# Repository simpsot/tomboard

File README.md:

# tomboard
My 34 split keyboard design. This is a learning project, so don't judge :-).

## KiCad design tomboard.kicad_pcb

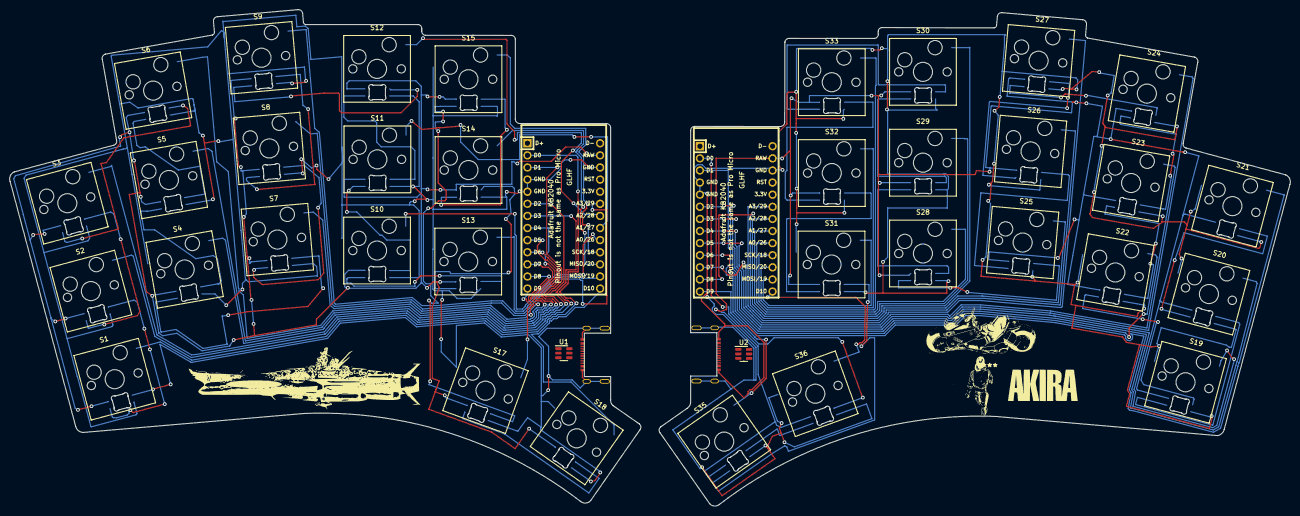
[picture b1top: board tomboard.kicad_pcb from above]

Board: 2 copper layers, 268.6 x 104.1 mm, 40 parts (0 on the bottom side), 75 nets.

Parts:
J0, J1: USB_C_Receptacle_USB2.0; USB-C_C168688
MCU1, MCU2: KB2040; kb2040
S1, S2, S3, S4, S5, S6, S7, S8, S9, S10, S11, S12, S13, S14, S15, S17, S18, S19, S20, S21, S22, S23, S24, S25, S26, S27, S28, S29, S30, S31, S32, S33, S35, S36: MX_SK6182; MX_1.00u_PCB_KailhSocket_mini-led
U1, U2: USBLC6-2SC6; SOT-23-6

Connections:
/+5v: MCU1.15 (RAW), S1.6 (VDD), S2.6 (VDD), S3.6 (VDD), S4.6 (VDD), S5.6 (VDD), S6.6 (VDD), S7.6 (VDD), S8.6 (VDD), S9.6 (VDD), S10.6 (VDD), S11.6 (VDD), S12.6 (VDD), S13.6 (VDD), S14.6 (VDD), S15.6 (VDD), S17.6 (VDD), S18.6 (VDD)
/GND: J0.A1 (GND), J0.S1 (SHIELD), MCU1.4 (GND), MCU1.5 (GND), MCU1.16 (GND), S1.1, S1.3 (VSS), S2.1, S2.3 (VSS), S3.1, S3.3 (VSS), S4.1, S4.3 (VSS), S5.1, S5.3 (VSS), S6.1, S6.3 (VSS), S7.1, S7.3 (VSS), S8.1, S8.3 (VSS), S9.1, S9.3 (VSS), S10.1, S10.3 (VSS), S11.1, S11.3 (VSS), S12.1, S12.3 (VSS), S13.1, S13.3 (VSS), S14.1, S14.3 (VSS), S15.1, S15.3 (VSS), S17.1, S17.3 (VSS), S18.1, S18.3 (VSS)
/led: MCU1.2 (D0), S1.4 (DIN)
/matrix_index_bottom: MCU1.22 (A0/26), S10.2
/matrix_index_home: MCU1.21 (A1/27), S11.2
/matrix_index_top: MCU1.20 (A2/28), S12.2
/matrix_inner_bottom: MCU1.25 (MOSI/19), S13.2
/matrix_inner_home: MCU1.24 (MISO/20), S14.2
/matrix_inner_top: MCU1.23 (SCK/18), S15.2
/matrix_middle_bottom: MCU1.12 (D8), S7.2
/matrix_middle_home: MCU1.11 (D7), S8.2
/matrix_middle_top: MCU1.19 (A3/29), S9.2
/matrix_pinky_bottom: MCU1.7 (D3), S1.2
/matrix_pinky_home: MCU1.6 (D2), S2.2
/matrix_pinky_top: MCU1.3 (D1), S3.2
/matrix_ring_bottom: MCU1.10 (D6), S4.2
/matrix_ring_home: MCU1.9 (D5), S5.2
/matrix_ring_top: MCU1.8 (D4), S6.2
/r_+5v: MCU2.15 (RAW), S19.6 (VDD), S20.6 (VDD), S21.6 (VDD), S22.6 (VDD), S23.6 (VDD), S24.6 (VDD), S25.6 (VDD), S26.6 (VDD), S27.6 (VDD), S28.6 (VDD), S29.6 (VDD), S30.6 (VDD), S31.6 (VDD), S32.6 (VDD), S33.6 (VDD), S35.6 (VDD), S36.6 (VDD)
/r_GND: J1.A1 (GND), J1.S1 (SHIELD), MCU2.4 (GND), MCU2.5 (GND), MCU2.16 (GND), S19.1, S19.3 (VSS), S20.1, S20.3 (VSS), S21.1, S21.3 (VSS), S22.1, S22.3 (VSS), S23.1, S23.3 (VSS), S24.1, S24.3 (VSS), S25.1, S25.3 (VSS), S26.1, S26.3 (VSS), S27.1, S27.3 (VSS), S28.1, S28.3 (VSS), S29.1, S29.3 (VSS), S30.1, S30.3 (VSS), S31.1, S31.3 (VSS), S32.1, S32.3 (VSS), S33.1, S33.3 (VSS), S35.1, S35.3 (VSS), S36.1, S36.3 (VSS), U2.2 (GND)
/r_VCC: J1.A4 (VBUS), MCU2.18 (3.3v), U2.5 (VBUS)
/r_led: MCU2.2 (D0), S36.4 (DIN)
/r_matrix_index_bottom: MCU2.22 (A0/26), S28.2
/r_matrix_index_home: MCU2.21 (A1/27), S29.2
/r_matrix_index_top: MCU2.20 (A2/28), S30.2
/r_matrix_inner_bottom: MCU2.25 (MOSI/19), S31.2
/r_matrix_inner_home: MCU2.24 (MISO/20), S32.2
/r_matrix_inner_top: MCU2.23 (SCK/18), S33.2
/r_matrix_middle_bottom: MCU2.12 (D8), S25.2
/r_matrix_middle_home: MCU2.19 (A3/29), S26.2
/r_matrix_middle_top: MCU2.11 (D7), S27.2
/r_matrix_pinky_bottom: MCU2.7 (D3), S19.2
/r_matrix_pinky_home: MCU2.6 (D2), S20.2
/r_matrix_pinky_top: MCU2.3 (D1), S21.2
/r_matrix_ring_bottom: MCU2.10 (D6), S22.2
/r_matrix_ring_home: MCU2.9 (D5), S23.2
/r_matrix_ring_top: MCU2.8 (D4), S24.2
/r_thumb_middle: MCU2.13 (D9), S35.2
/r_thumb_reachy: MCU2.26 (D10), S36.2
/thumb_middle: MCU1.13 (D9), S17.2
/thumb_reachy: MCU1.26 (D10), S18.2
unnamed: J1.A6 (D+), J1.B6 (D+), U2.1 (I/O1)
unnamed: J1.A7 (D-), J1.B7 (D-)
unnamed: S1.5 (DOUT), S2.4 (DIN)
unnamed: S2.5 (DOUT), S3.4 (DIN)
unnamed: S3.5 (DOUT), S6.4 (DIN)
unnamed: S4.4 (DIN), S5.5 (DOUT)
unnamed: S4.5 (DOUT), S7.4 (DIN)
unnamed: S5.4 (DIN), S6.5 (DOUT)
unnamed: S7.5 (DOUT), S8.4 (DIN)
unnamed: S8.5 (DOUT), S9.4 (DIN)
unnamed: S10.4 (DIN), S11.5 (DOUT)
unnamed: S10.5 (DOUT), S13.4 (DIN)
unnamed: S11.4 (DIN), S12.5 (DOUT)
unnamed: S9.5 (DOUT), S12.4 (DIN)
unnamed: S13.5 (DOUT), S14.4 (DIN)
unnamed: S14.5 (DOUT), S15.4 (DIN)
unnamed: S15.5 (DOUT), S17.4 (DIN)
unnamed: S17.5 (DOUT), S18.4 (DIN)
unnamed: S19.4 (DIN), S22.5 (DOUT)
unnamed: S19.5 (DOUT), S20.4 (DIN)
unnamed: S20.5 (DOUT), S21.4 (DIN)
unnamed: S22.4 (DIN), S23.5 (DOUT)
unnamed: S23.4 (DIN), S24.5 (DOUT)
unnamed: S24.4 (DIN), S27.5 (DOUT)
unnamed: S25.4 (DIN), S28.5 (DOUT)
unnamed: S25.5 (DOUT), S26.4 (DIN)
unnamed: S26.5 (DOUT), S27.4 (DIN)
unnamed: S28.4 (DIN), S29.5 (DOUT)
unnamed: S29.4 (DIN), S30.5 (DOUT)
unnamed: S30.4 (DIN), S33.5 (DOUT)
unnamed: S31.4 (DIN), S35.5 (DOUT)
unnamed: S31.5 (DOUT), S32.4 (DIN)
unnamed: S32.5 (DOUT), S33.4 (DIN)
unnamed: S35.4 (DIN), S36.5 (DOUT)

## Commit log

2022-08-19 adding board to github
